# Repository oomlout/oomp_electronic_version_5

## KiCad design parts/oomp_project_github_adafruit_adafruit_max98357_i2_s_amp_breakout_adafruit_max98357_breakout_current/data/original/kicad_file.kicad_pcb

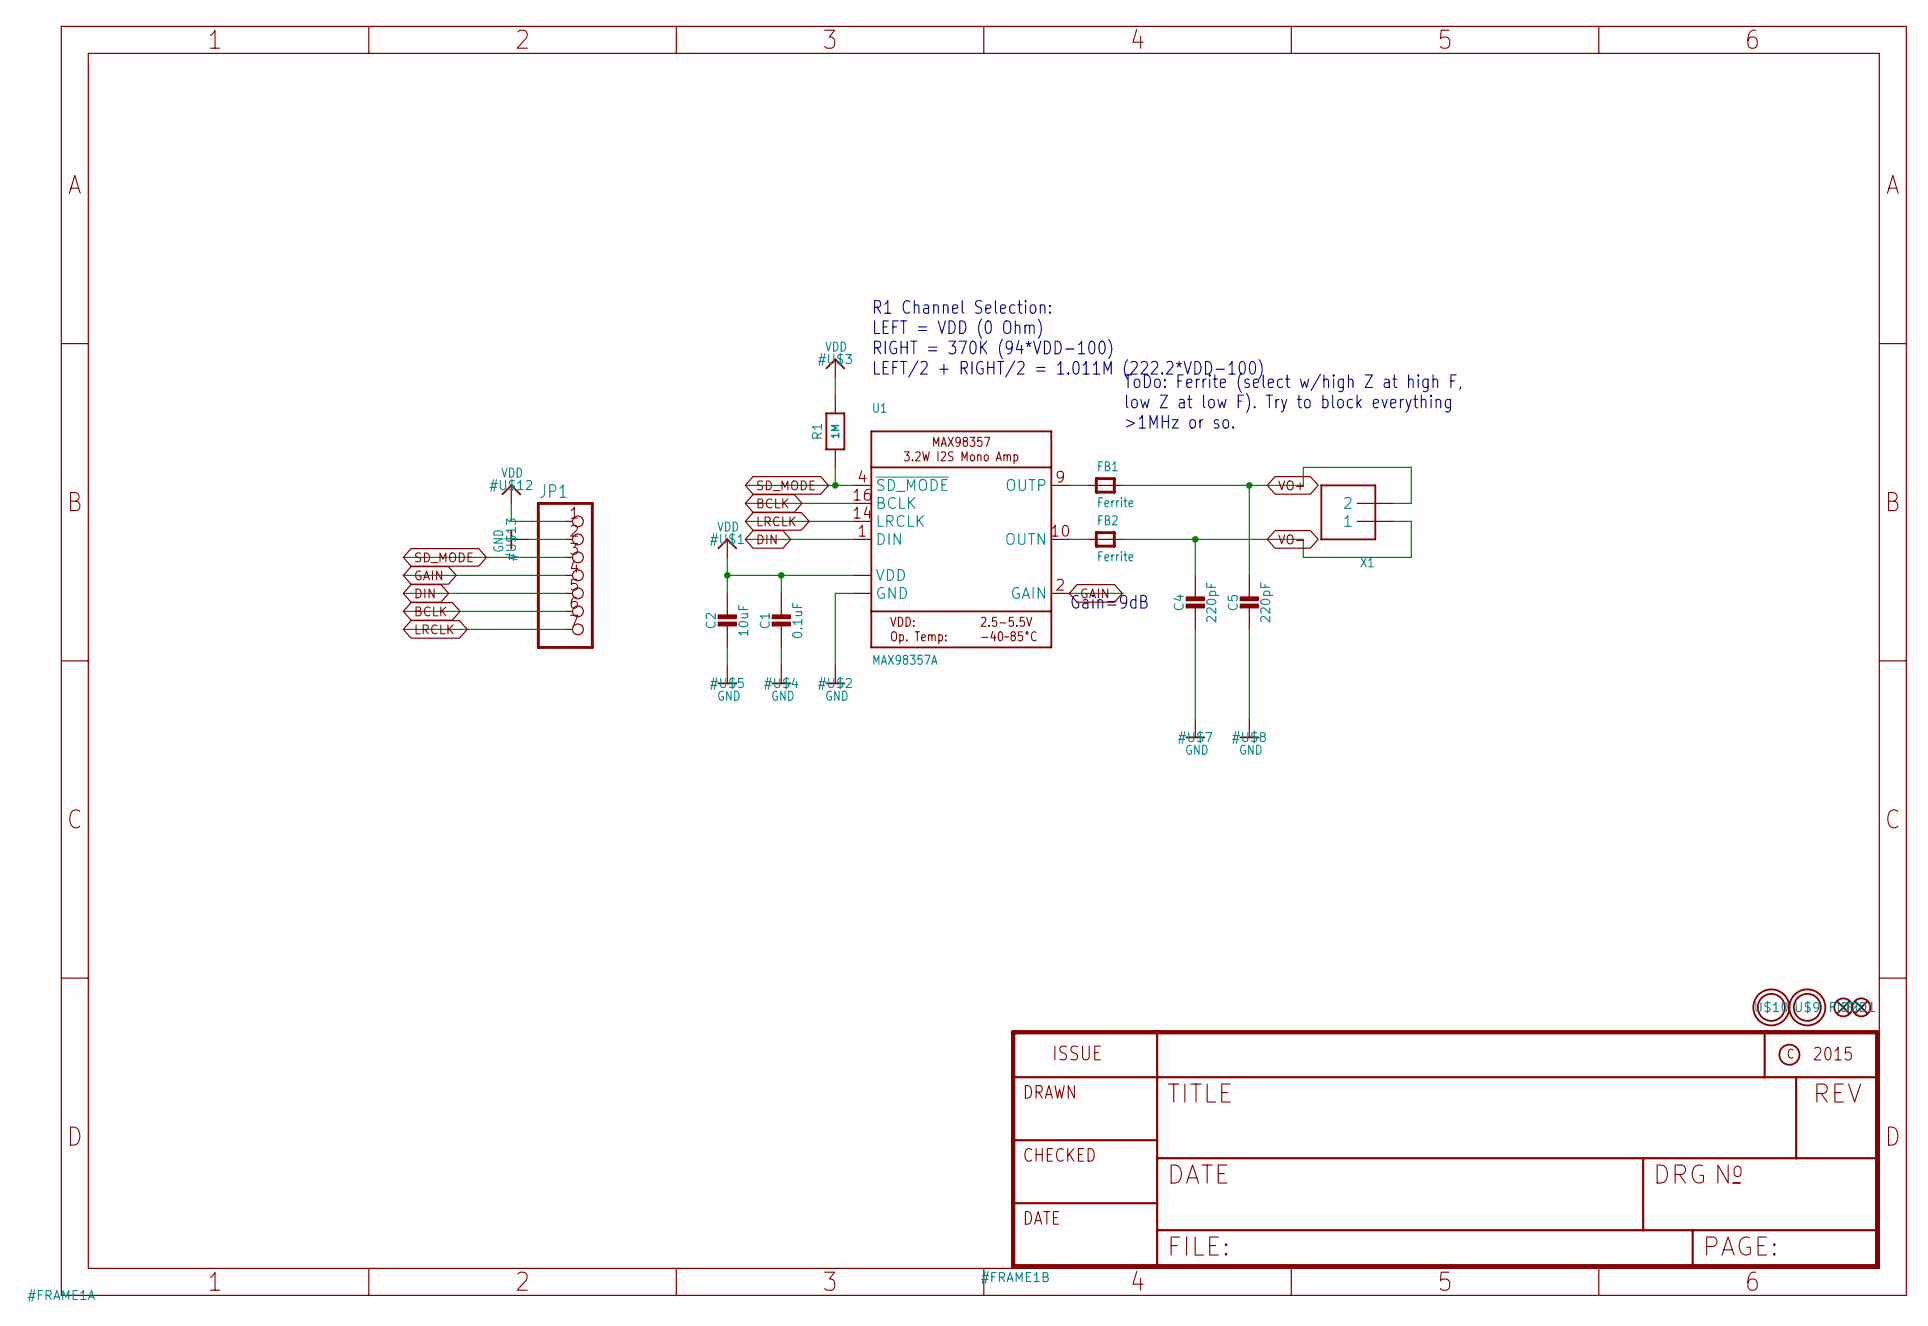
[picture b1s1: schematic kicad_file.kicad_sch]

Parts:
C1: 0.1uF; 0805-NO
C2: 10uF; 0805-NO
C4, C5: 220pF; 0805-NO
FB1, FB2: Ferrite; 0805-NO
FID1, FID2: FIDUCIAL""; FIDUCIAL_1MM
JP1: HEADER-1X7THICKER; 1X07_ROUND_76
R1: 1M; 0805-NO
U1: MAX98357A; QFN16_3MM
U$9, U$10: MOUNTINGHOLE2.5; MOUNTINGHOLE_2.5_PLATED
X1: TERMBLOCK_1X2; TERMBLOCK_1X2-3.5MM

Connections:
BCLK: JP1.6, U1.16 (BCLK)
DIN: JP1.5, U1.1 (DIN)
GAIN: JP1.4, U1.2 (GAIN)
GND: C1.2, C2.2, C4.2, C5.2, JP1.2, U1.3 (GND), U1.11 (GND), U1.15 (GND), U1.THERMAL (GND)
LRCLK: JP1.7, U1.14 (LRCLK)
unnamed: FB2.1, U1.10 (OUTN)
unnamed: FB1.1, U1.9 (OUTP)
SD_MODE: JP1.3, R1.1, U1.4 (~SD_MODE)
VDD: C1.1, C2.1, JP1.1, R1.2, U1.7 (VDD), U1.8 (VDD)
VO+: C5.1, FB1.2, X1.2
VO-: C4.1, FB2.2, X1.1

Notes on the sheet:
Gain=9dB
ToDo: Ferrite (select w/high Z at high F, low Z at low F). Try to block everything >1MHz or so.
R1 Channel Selection: LEFT = VDD (0 Ohm) RIGHT = 370K (94*VDD-100) LEFT/2 + RIGHT/2 = 1.011M (222.2*VDD-100)

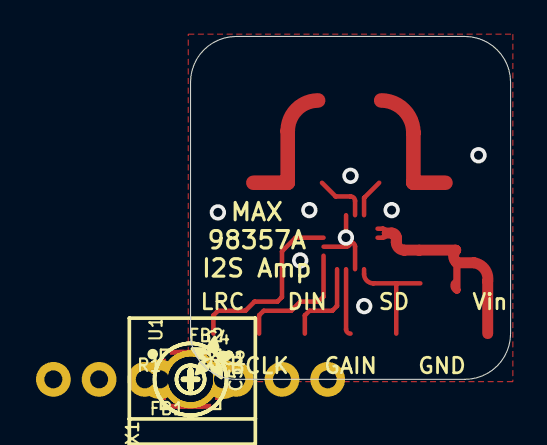
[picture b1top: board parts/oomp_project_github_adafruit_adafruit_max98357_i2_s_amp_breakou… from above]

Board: 2 copper layers, 17.8 x 19.1 mm, 18 parts (1 on the bottom side), 11 nets.

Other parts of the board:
U$6: SYMBOL_PLUS
U$11: SYMBOL_MINUS
U$14: ADAFRUIT_2.5MM
U$15: PCBFEAT-REV-040

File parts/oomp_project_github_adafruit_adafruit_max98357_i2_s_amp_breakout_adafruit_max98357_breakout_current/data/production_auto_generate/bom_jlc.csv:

Comment,Designator,Footprint,LCSC Part #
,JP1,Adafruit MAX98357 Breakout-import-fps:1X07_ROUND_76,C7501585
,U$14,Adafruit MAX98357 Breakout-import-fps:ADAFRUIT_2.5MM,
,U$15,Adafruit MAX98357 Breakout-import-fps:PCBFEAT-REV-040,
,U$11,Adafruit MAX98357 Breakout-import-fps:SYMBOL_MINUS,
,U$6,Adafruit MAX98357 Breakout-import-fps:SYMBOL_PLUS,
,X1,Adafruit MAX98357 Breakout-import-fps:TERMBLOCK_1X2-3.5MM,
0.1uF,C1,Adafruit MAX98357 Breakout-import-fps:0805-NO,
10uF,C2,Adafruit MAX98357 Breakout-import-fps:0805-NO,
1M,R1,Adafruit MAX98357 Breakout-import-fps:0805-NO,C2933280
220pF,"C4,C5",Adafruit MAX98357 Breakout-import-fps:0805-NO,
Ferrite,"FB1,FB2",Adafruit MAX98357 Breakout-import-fps:0805-NO,
MAX98357A,U1,Adafruit MAX98357 Breakout-import-fps:QFN16_3MM,

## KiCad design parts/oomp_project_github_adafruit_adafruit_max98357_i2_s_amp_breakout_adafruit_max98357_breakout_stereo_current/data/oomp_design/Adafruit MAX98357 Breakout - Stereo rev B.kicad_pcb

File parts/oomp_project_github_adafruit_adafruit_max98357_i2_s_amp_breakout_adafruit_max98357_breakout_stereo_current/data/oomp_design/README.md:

# OOMP KiCad design copy

Open `Adafruit MAX98357 Breakout - Stereo rev B.kicad_pro` (or the `.kicad_pcb` / `.kicad_sch`) in KiCad. Local OOMP libraries are under `libraries/`. Original inputs are preserved in [../original/](../original/).

Only verified unchanged installed KiCad defaults were renamed. Modified, custom, unmatched and unavailable items remain unchanged. Soldering variants are never swapped during conversion. Existing pad coordinates, nets and UUIDs are preserved.

See [conversion_report.yaml](conversion_report.yaml) for every conversion and skip. Copy this directory before editing; regeneration refuses to overwrite edited design files.

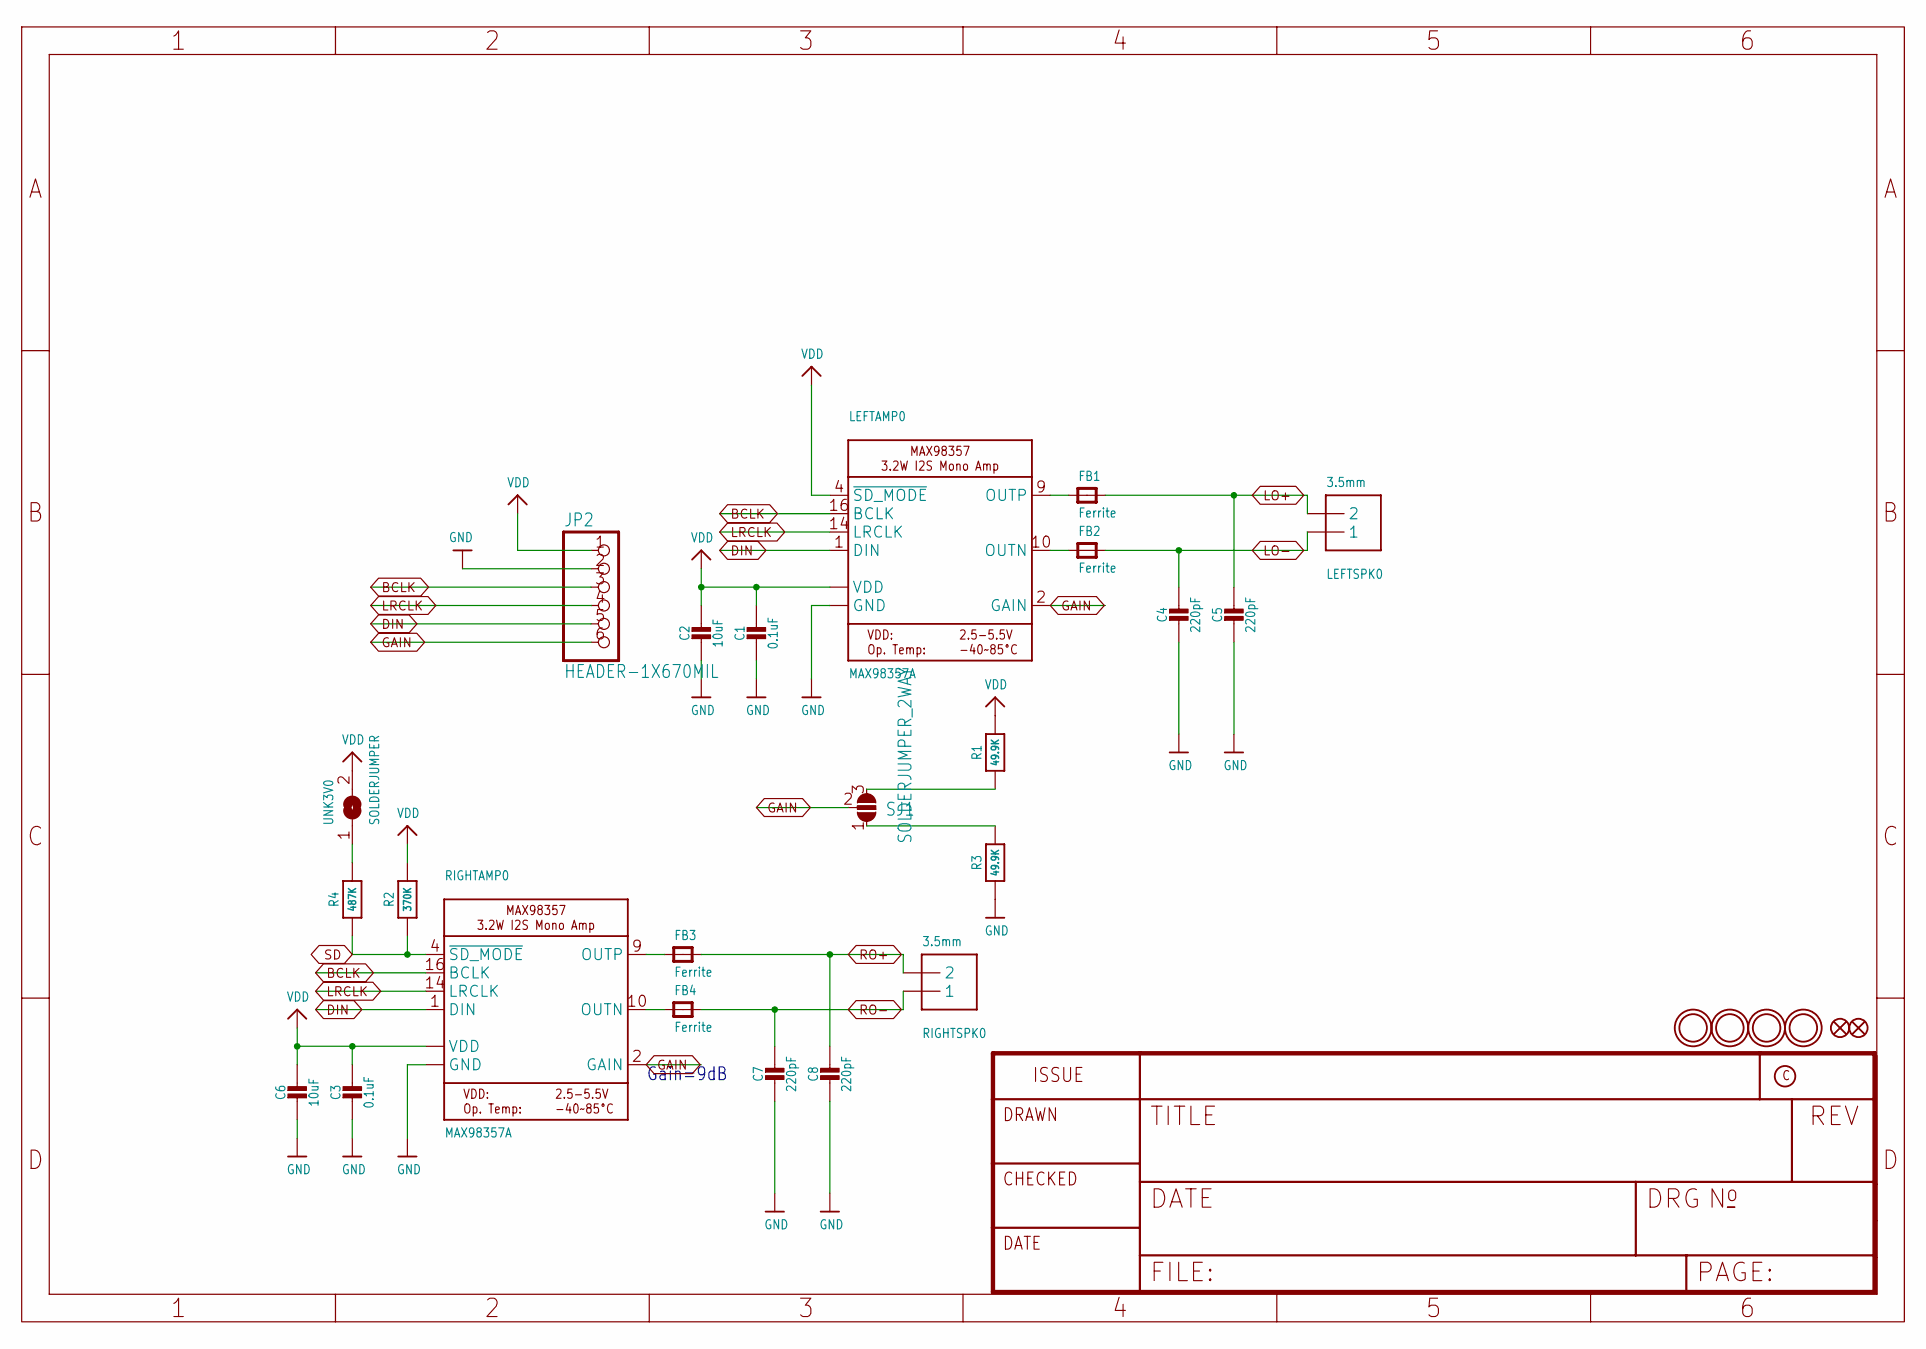
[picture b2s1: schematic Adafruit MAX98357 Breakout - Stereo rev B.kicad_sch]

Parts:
C1, C3: 0.1uF; 0603-NO
C2, C6: 10uF; 0805-NO
C4, C5, C7, C8: 220pF; 0603-NO
FB1, FB2, FB3, FB4: Ferrite; 0603-NO
FID1, FID2: FIDUCIAL_0.5MM
JP2: HEADER-1X670MIL; 1X06_ROUND_70
LEFTAMP0: MAX98357A; QFN16_3MM
LEFTSPK0: 3.5mm; TERMBLOCK_1X2-3.5MM
R1, R3: 49.9K; 0603-NO
R2: 370K; 0603-NO
R4: 487K; 0603-NO
RIGHTAMP0: MAX98357A; QFN16_3MM
RIGHTSPK0: 3.5mm; TERMBLOCK_1X2-3.5MM
SJ1: SOLDERJUMPER_2WAY; SOLDERJUMPER_2WAY_OPEN_NOPASTE
U$9, U$10, U$23, U$24: MOUNTINGHOLE2.5; MOUNTINGHOLE_2.5_PLATED
UNK3V0: SOLDERJUMPER; SOLDERJUMPER_ARROW_NOPASTE

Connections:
BCLK: JP2.3, LEFTAMP0.16 (BCLK), RIGHTAMP0.16 (BCLK)
DIN: JP2.5, LEFTAMP0.1 (DIN), RIGHTAMP0.1 (DIN)
GAIN: JP2.6, LEFTAMP0.2 (GAIN), RIGHTAMP0.2 (GAIN), SJ1.2
GND: C1.2, C2.2, C3.2, C4.2, C5.2, C6.2, C7.2, C8.2, JP2.2, LEFTAMP0.3 (GND), LEFTAMP0.11 (GND), LEFTAMP0.15 (GND), LEFTAMP0.THERMAL (GND), R3.1, RIGHTAMP0.3 (GND), RIGHTAMP0.11 (GND), RIGHTAMP0.15 (GND), RIGHTAMP0.THERMAL (GND)
LO+: C5.1, FB1.2, LEFTSPK0.2
LO-: C4.1, FB2.2, LEFTSPK0.1
LRCLK: JP2.4, LEFTAMP0.14 (LRCLK), RIGHTAMP0.14 (LRCLK)
unnamed: FB4.1, RIGHTAMP0.10 (OUTN)
unnamed: FB3.1, RIGHTAMP0.9 (OUTP)
unnamed: R3.2, SJ1.1
unnamed: R4.2, UNK3V0.1
unnamed: FB2.1, LEFTAMP0.10 (OUTN)
unnamed: FB1.1, LEFTAMP0.9 (OUTP)
unnamed: R1.1, SJ1.3
RO+: C8.1, FB3.2, RIGHTSPK0.2
RO-: C7.1, FB4.2, RIGHTSPK0.1
SD: R2.1, R4.1, RIGHTAMP0.4 (~SD_MODE)
VDD: C1.1, C2.1, C3.1, C6.1, JP2.1, LEFTAMP0.4 (~SD_MODE), LEFTAMP0.7 (VDD), LEFTAMP0.8 (VDD), R1.2, R2.2, RIGHTAMP0.7 (VDD), RIGHTAMP0.8 (VDD), UNK3V0.2

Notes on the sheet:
Gain=9dB

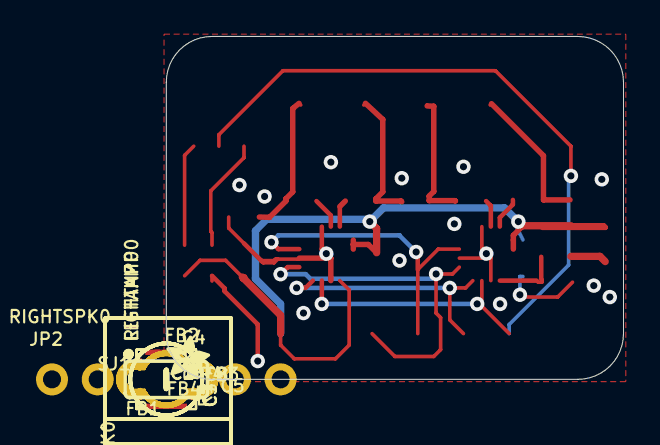
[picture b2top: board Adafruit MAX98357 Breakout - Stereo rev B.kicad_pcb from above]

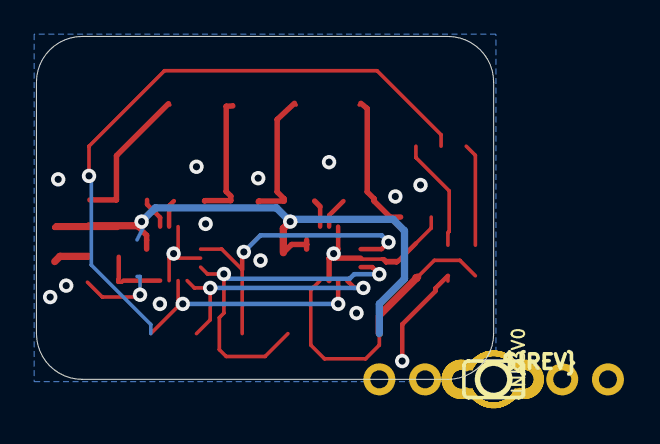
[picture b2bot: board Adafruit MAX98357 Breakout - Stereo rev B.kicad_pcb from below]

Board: 2 copper layers, 25.4 x 19.1 mm, 51 parts (6 on the bottom side), 18 nets.

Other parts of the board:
PLABEL0: PLABEL0
PLABEL1: PLABEL1
PLABEL2: PLABEL2
PLABEL3: PLABEL3
PLABEL4: PLABEL4
PLABEL5: PLABEL5
PLABEL6: PLABEL6
PLABEL7: PLABEL7
PLABEL8: PLABEL8
PLABEL9: PLABEL9
PLABEL10: PLABEL10
PLABEL11: PLABEL11
PLABEL12: PLABEL12
PLABEL13: PLABEL13
PLABEL14: PLABEL14
PLABEL15: PLABEL15
PLABEL16: PLABEL16
PLABEL17: PLABEL17
PLABEL18: PLABEL18
PLABEL19: PLABEL19
U$14: ADAFRUIT_2.5MM
U$15: PCBFEAT-REV-040

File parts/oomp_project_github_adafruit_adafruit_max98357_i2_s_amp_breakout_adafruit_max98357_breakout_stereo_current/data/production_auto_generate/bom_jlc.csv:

Comment,Designator,Footprint,LCSC Part #
,JP2,Adafruit MAX98357 Breakout - Stereo rev B-import-fps:1X06_ROUND_70,C37208
,U$14,Adafruit MAX98357 Breakout - Stereo rev B-import-fps:ADAFRUIT_2.5MM,
,U$15,Adafruit MAX98357 Breakout - Stereo rev B-import-fps:PCBFEAT-REV-040,
,PLABEL0,Adafruit MAX98357 Breakout - Stereo rev B-import-fps:PLABEL0,
,PLABEL1,Adafruit MAX98357 Breakout - Stereo rev B-import-fps:PLABEL1,
,PLABEL10,Adafruit MAX98357 Breakout - Stereo rev B-import-fps:PLABEL10,
,PLABEL11,Adafruit MAX98357 Breakout - Stereo rev B-import-fps:PLABEL11,
,PLABEL12,Adafruit MAX98357 Breakout - Stereo rev B-import-fps:PLABEL12,
,PLABEL13,Adafruit MAX98357 Breakout - Stereo rev B-import-fps:PLABEL13,
,PLABEL14,Adafruit MAX98357 Breakout - Stereo rev B-import-fps:PLABEL14,
,PLABEL15,Adafruit MAX98357 Breakout - Stereo rev B-import-fps:PLABEL15,
,PLABEL16,Adafruit MAX98357 Breakout - Stereo rev B-import-fps:PLABEL16,
,PLABEL17,Adafruit MAX98357 Breakout - Stereo rev B-import-fps:PLABEL17,
,PLABEL18,Adafruit MAX98357 Breakout - Stereo rev B-import-fps:PLABEL18,
,PLABEL19,Adafruit MAX98357 Breakout - Stereo rev B-import-fps:PLABEL19,
,PLABEL2,Adafruit MAX98357 Breakout - Stereo rev B-import-fps:PLABEL2,
,PLABEL3,Adafruit MAX98357 Breakout - Stereo rev B-import-fps:PLABEL3,
,PLABEL4,Adafruit MAX98357 Breakout - Stereo rev B-import-fps:PLABEL4,
,PLABEL5,Adafruit MAX98357 Breakout - Stereo rev B-import-fps:PLABEL5,
,PLABEL6,Adafruit MAX98357 Breakout - Stereo rev B-import-fps:PLABEL6,
,PLABEL7,Adafruit MAX98357 Breakout - Stereo rev B-import-fps:PLABEL7,
,PLABEL8,Adafruit MAX98357 Breakout - Stereo rev B-import-fps:PLABEL8,
,PLABEL9,Adafruit MAX98357 Breakout - Stereo rev B-import-fps:PLABEL9,
,UNK3V0,Adafruit MAX98357 Breakout - Stereo rev B-import-fps:SOLDERJUMPER_ARROW_NOPASTE,
0.1uF,"C1,C3",Adafruit MAX98357 Breakout - Stereo rev B-import-fps:0603-NO,C14663
10uF,"C2,C6",Adafruit MAX98357 Breakout - Stereo rev B-import-fps:0805-NO,
220pF,"C4,C5,C7,C8",Adafruit MAX98357 Breakout - Stereo rev B-import-fps:0603-NO,
3.5mm,"LEFTSPK0,RIGHTSPK0",Adafruit MAX98357 Breakout - Stereo rev B-import-fps:TERMBLOCK_1X2-3.5MM,
370K,R2,Adafruit MAX98357 Breakout - Stereo rev B-import-fps:0603-NO,
487K,R4,Adafruit MAX98357 Breakout - Stereo rev B-import-fps:0603-NO,
49.9K,"R1,R3",Adafruit MAX98357 Breakout - Stereo rev B-import-fps:0603-NO,
Ferrite,"FB1,FB2,FB3,FB4",Adafruit MAX98357 Breakout - Stereo rev B-import-fps:0603-NO,
MAX98357A,"LEFTAMP0,RIGHTAMP0",Adafruit MAX98357 Breakout - Stereo rev B-import-fps:QFN16_3MM,

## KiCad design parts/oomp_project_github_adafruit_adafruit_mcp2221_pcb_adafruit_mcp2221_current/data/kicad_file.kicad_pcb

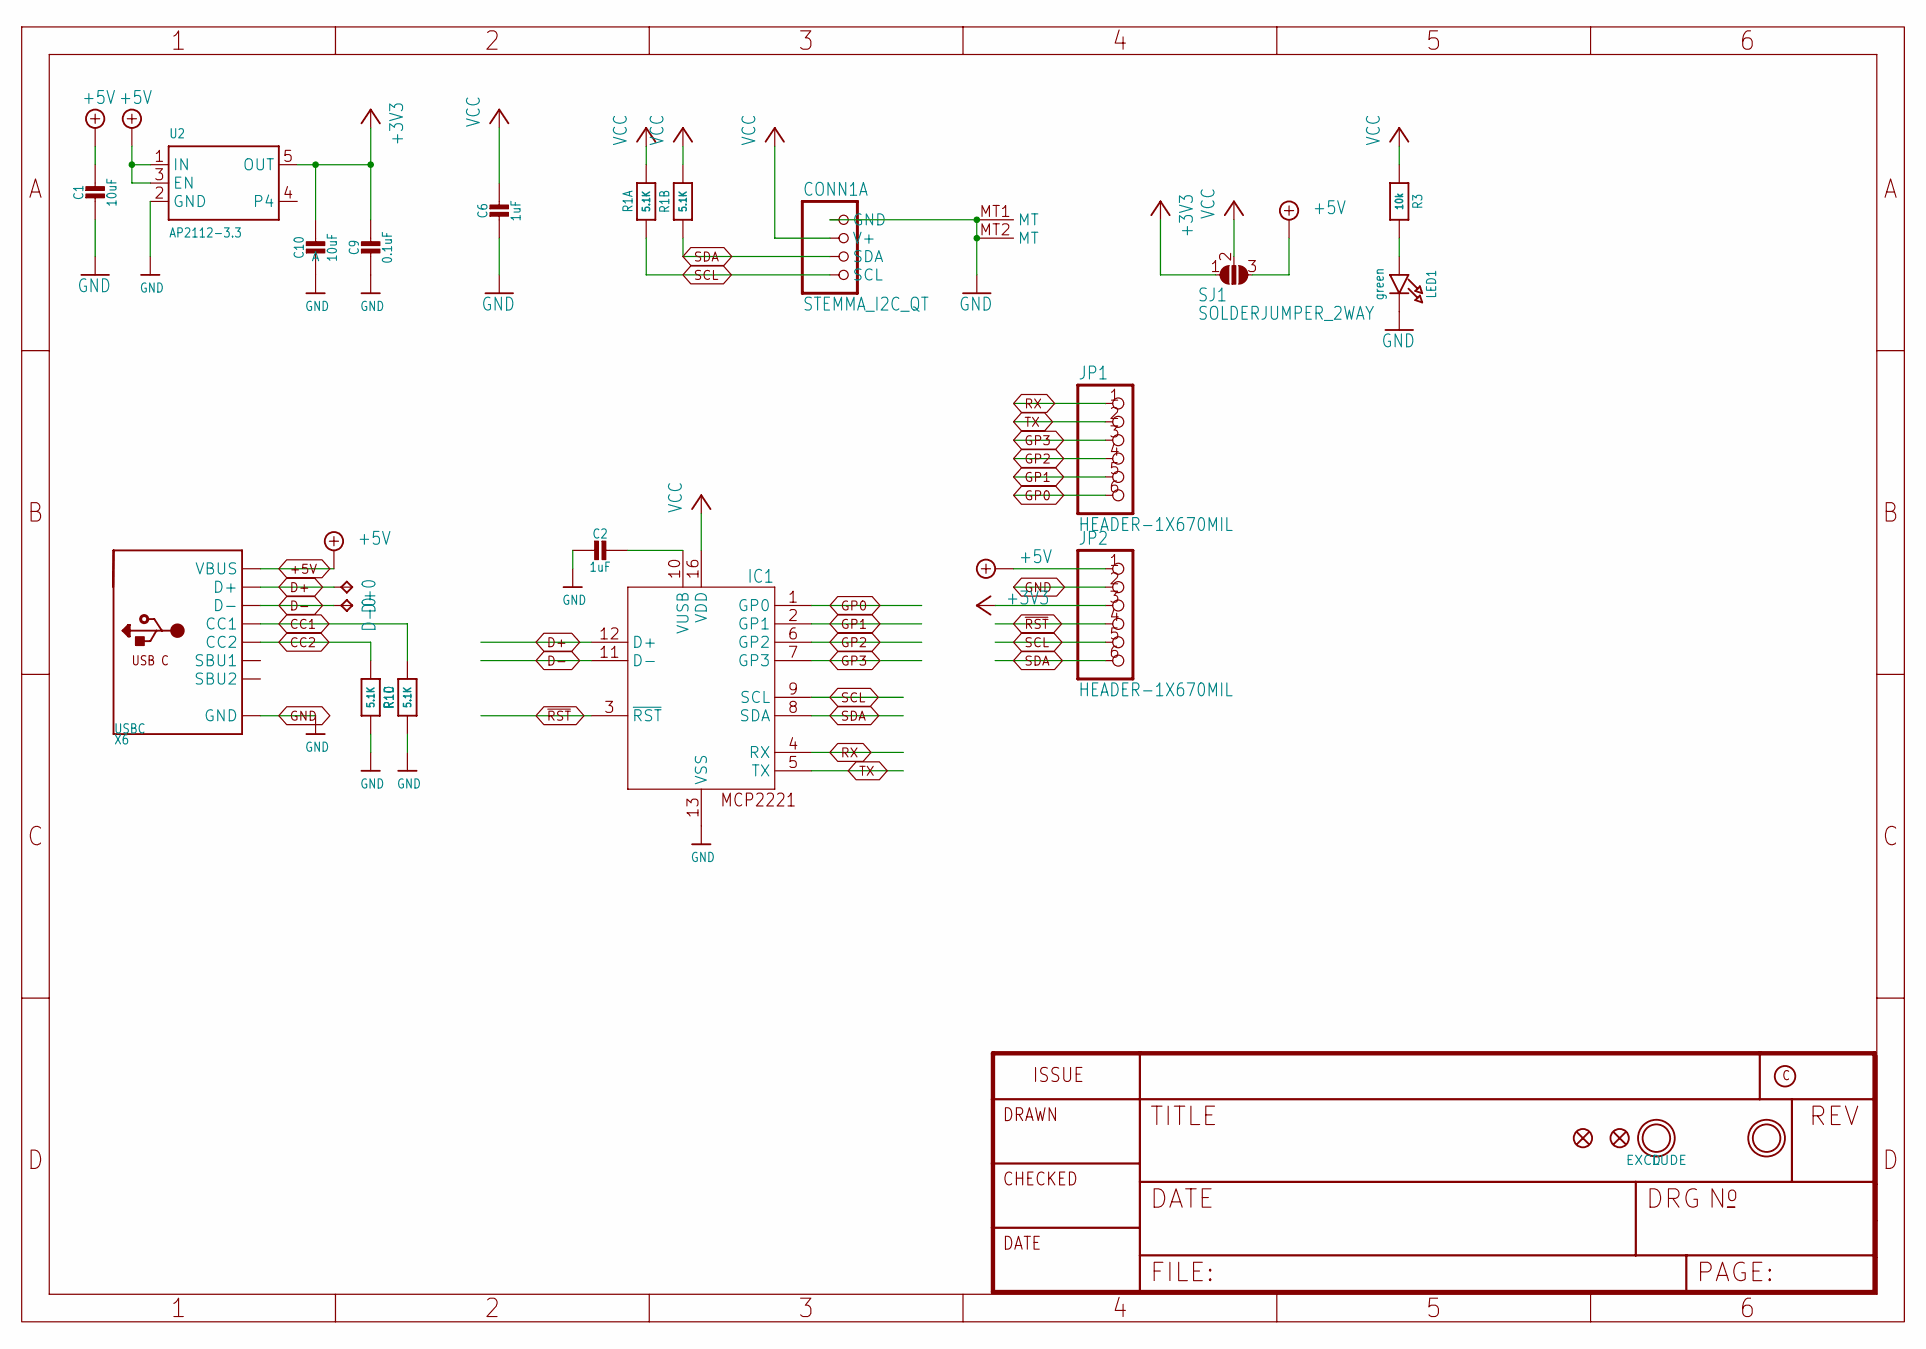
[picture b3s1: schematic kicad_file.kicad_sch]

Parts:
C1, C10: 10uF; 0805-NO
C2, C6: 1uF; 0603-NO
C9: 0.1uF; 0603-NO
CONN1: STEMMA_I2C_QT; JST_SH4
D+0: TPTP17R; TP17R
D-0: TPTP17R; TP17R
FID1, FID2: FIDUCIAL_1MM
IC1: MCP2221_ML; QFN16_4MM
JP1, JP2: HEADER-1X670MIL; 1X06_ROUND_70
LED1: green; CHIPLED_0603_NOOUTLINE
R1: 5.1K; RESPACK_4X0603
R3: 10k; 0603-NO
SJ1: SOLDERJUMPER_2WAY; SOLDERJUMPER_2WAY_OPEN_NOPASTE
U2: AP2112-3.3; SOT23-5
U$6, U$7: MOUNTINGHOLE2.5; MOUNTINGHOLE_2.5_PLATED
X6: USBC; USB_C_CUSB31-CFM2AX-01-X

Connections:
+3V3: C9.1, C10.1, JP2.3, SJ1.1, U2.5 (OUT)
+5V: C1.1, JP2.1, SJ1.3, U2.1 (IN), U2.3 (EN), X6.A4B9 (VBUS), X6.B4A9 (VBUS)
CC1: R1.6 (2), X6.A5 (CC1)
CC2: R1.4 (1), X6.B5 (CC2)
D+: D+0.TP, IC1.12 (D+), X6.A6 (D+), X6.B6 (D+)
D-: D-0.TP, IC1.11 (D-), X6.A7 (D-), X6.B7 (D-)
GND: C1.2, C2.2, C6.2, C9.2, C10.2, CONN1.1 (GND), CONN1.MT1 (MT), CONN1.MT2 (MT), IC1.13 (VSS), JP2.2, LED1.C, R1.3 (1), R1.5 (2), U2.2 (GND), X6.A1B12 (GND), X6.B1A12 (GND)
GP0: IC1.1 (GP0), JP1.6
GP1: IC1.2 (GP1), JP1.5
GP2: IC1.6 (GP2), JP1.4
GP3: IC1.7 (GP3), JP1.3
unnamed: C2.1, IC1.10 (VUSB)
unnamed: LED1.A, R3.2
RX: IC1.4 (RX), JP1.1
SCL: CONN1.4 (SCL), IC1.9 (SCL), JP2.5, R1.1
SDA: CONN1.3 (SDA), IC1.8 (SDA), JP2.6, R1.2 (1)
TX: IC1.5 (TX), JP1.2
VCC: C6.1, CONN1.2 (V+), IC1.16 (VDD), R1.7 (2), R1.8 (2), R3.1, SJ1.2
~RST: IC1.3 (~RST), JP2.4

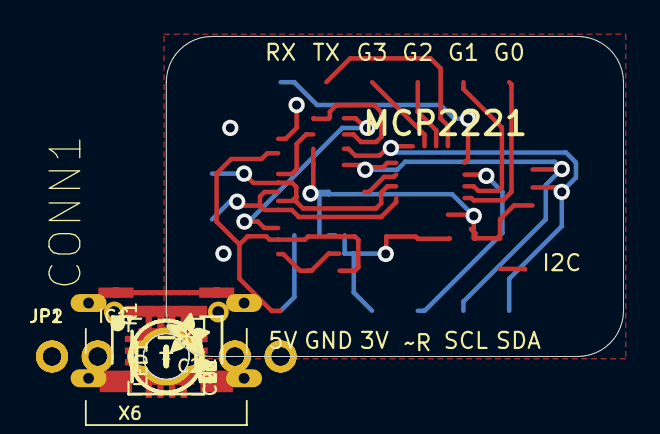
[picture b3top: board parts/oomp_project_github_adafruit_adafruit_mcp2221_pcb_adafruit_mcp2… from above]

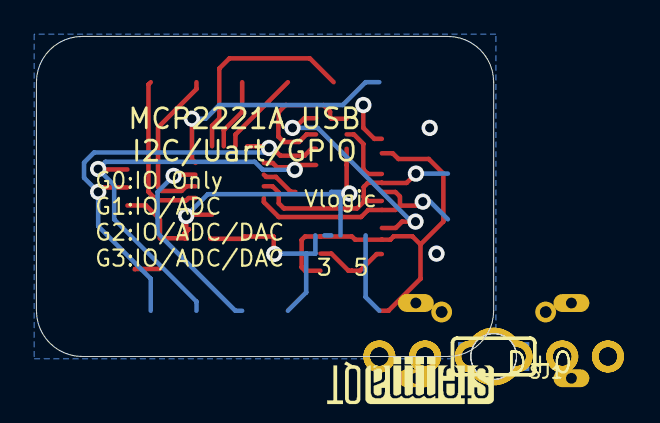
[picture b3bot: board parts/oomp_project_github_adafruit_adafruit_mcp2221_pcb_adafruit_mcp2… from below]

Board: 2 copper layers, 25.4 x 17.8 mm, 25 parts (4 on the bottom side), 19 nets.

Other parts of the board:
U$2: ADAFRUIT_2.5MM
U$3: STEMMAQT
UNK_HOLE_0: dummyfp0
UNK_HOLE_1: dummyfp1

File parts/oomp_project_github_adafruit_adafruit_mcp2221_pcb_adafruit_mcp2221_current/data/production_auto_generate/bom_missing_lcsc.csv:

Designator,Comment,Footprint,OOMP ID,Reason
C1,10uF,Adafruit MCP2221-import-fps:0805-NO,electronic_capacitor_0805_10_micro_farad,No verified LCSC part number
C10,10uF,Adafruit MCP2221-import-fps:0805-NO,electronic_capacitor_0805_10_micro_farad,No verified LCSC part number
D+0,TPTP17R,Adafruit MCP2221-import-fps:TP17R,,No verified LCSC part number
D-0,TPTP17R,Adafruit MCP2221-import-fps:TP17R,,No verified LCSC part number
IC1,MCP2221_ML,Adafruit MCP2221-import-fps:QFN16_4MM,,No verified LCSC part number
LED1,green,Adafruit MCP2221-import-fps:CHIPLED_0603_NOOUTLINE,electronic_led_0603_green,No verified LCSC part number
U2,AP2112-3.3,Adafruit MCP2221-import-fps:SOT23-5,,No verified LCSC part number
U$2,,Adafruit MCP2221-import-fps:ADAFRUIT_2.5MM,,No verified LCSC part number
U$3,,Adafruit MCP2221-import-fps:STEMMAQT,,No verified LCSC part number
X6,USBC,Adafruit MCP2221-import-fps:USB_C_CUSB31-CFM2AX-01-X,,No verified LCSC part number

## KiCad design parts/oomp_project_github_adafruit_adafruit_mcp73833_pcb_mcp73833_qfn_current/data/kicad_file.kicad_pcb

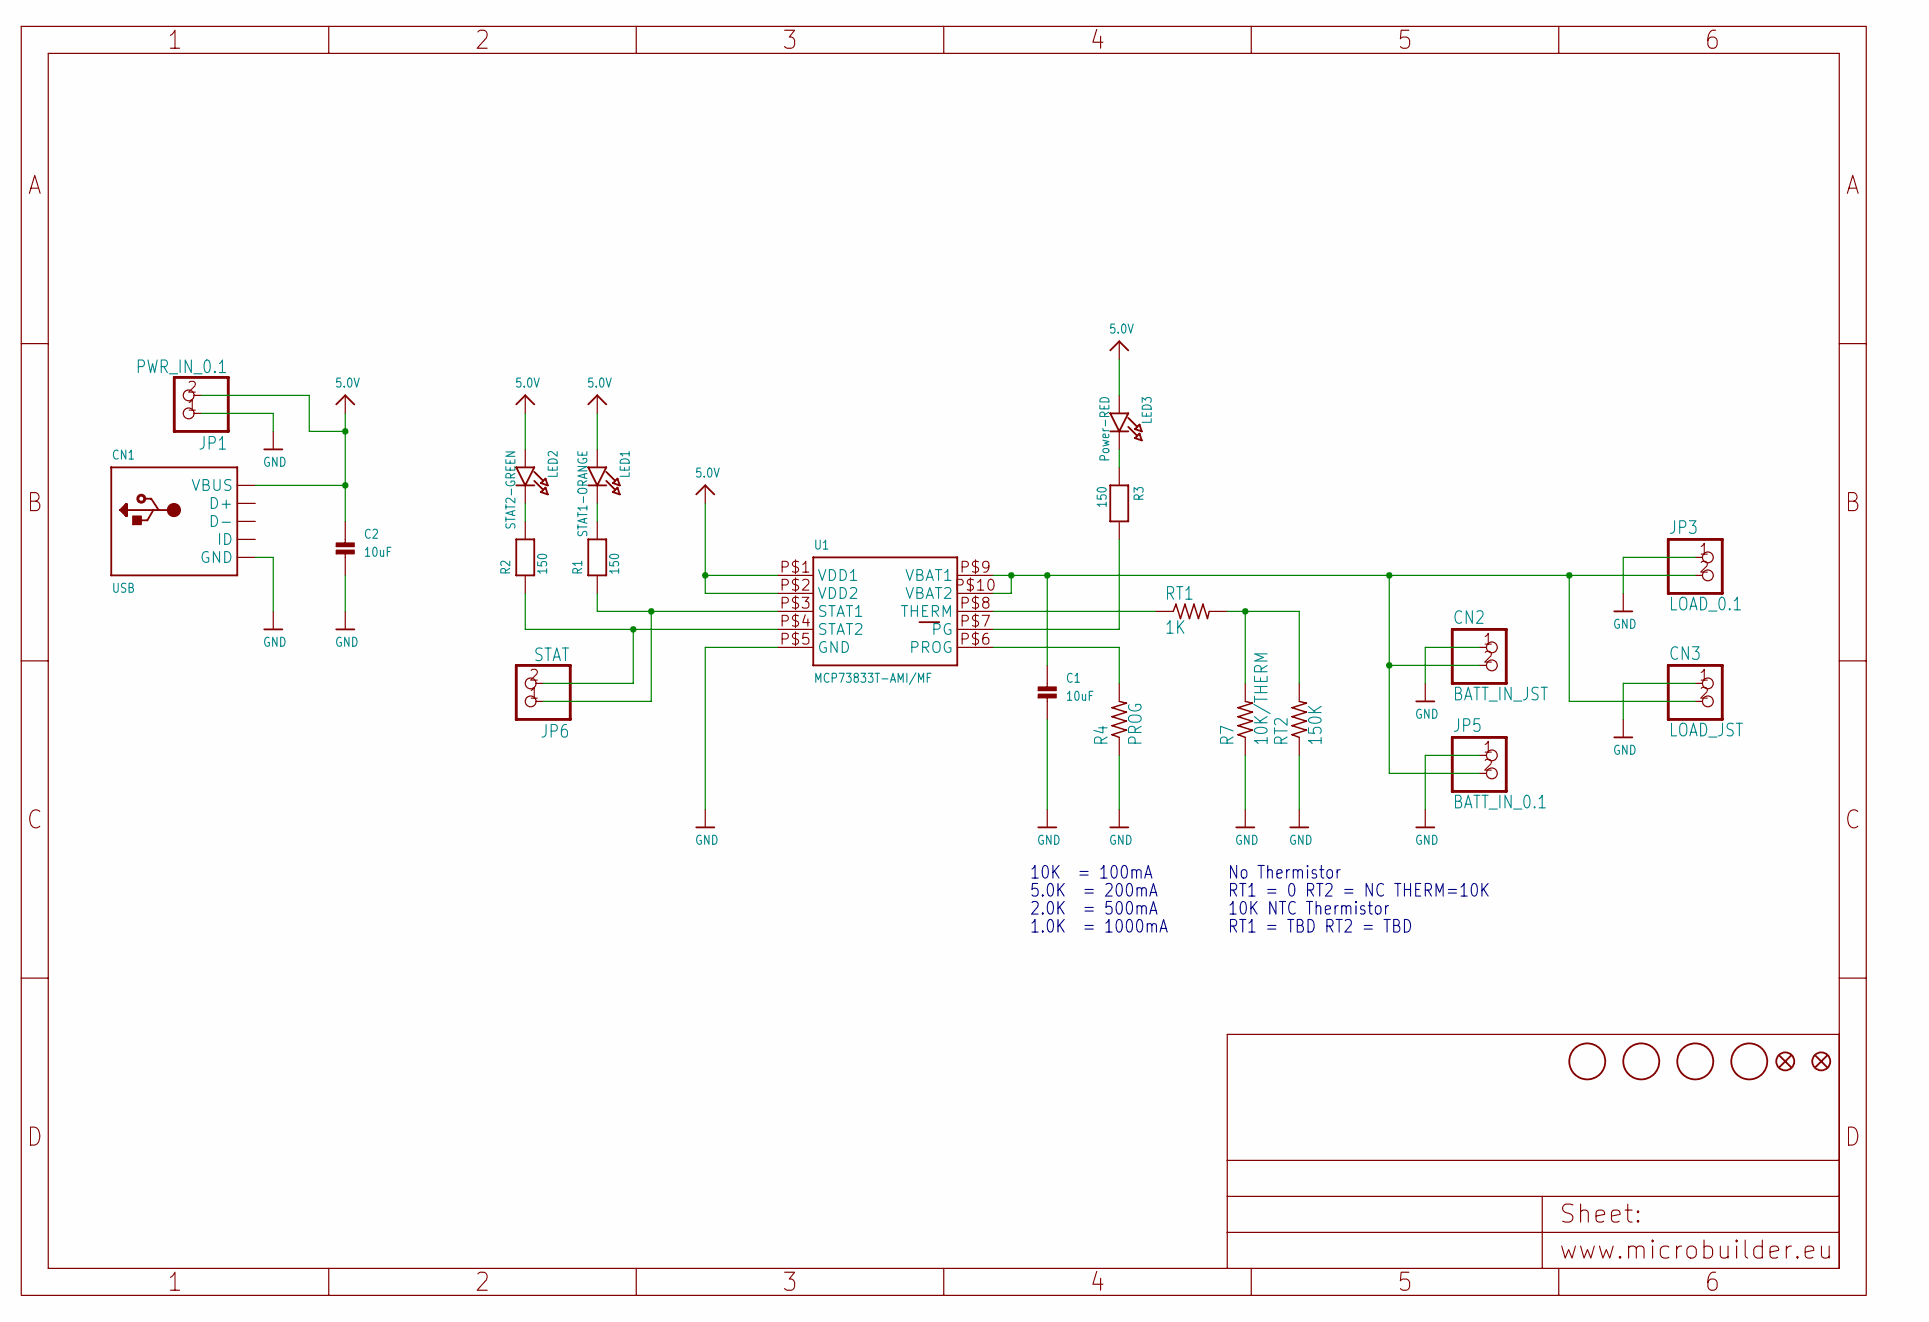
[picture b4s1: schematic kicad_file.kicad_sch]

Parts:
C1, C2: 10uF; 0805
CN1: USB; USB-MINIB_LARGER
CN2: BATT_IN_JST; JSTPH2
CN3: LOAD_JST; JSTPH2
JP1: PWR_IN_0.1; 1X02_OVAL
JP2, JP4: FIDUCIAL1.5X3; FIDUCIAL-1X2.5
JP3: LOAD_0.1; 1X02_OVAL
JP5: BATT_IN_0.1; 1X02_OVAL
JP6: STAT; 1X02_OVAL
LED1: STAT1-ORANGE; CHIPLED_0805
LED2: STAT2-GREEN; CHIPLED_0805
LED3: Power-RED; CHIPLED_0805
R1, R2, R3: 150; 0805
R4: PROG; 0805-THM
R7: 10K/THERM; 0805-THM
RT1: 1K; R0805
RT2: 150K; R0805
U1: MCP73833T-AMI/MF; DFN10_3X3MM
U$11, U$16, U$18, U$19: MOUNTINGHOLE2.0; MOUNTINGHOLE_2.0_PLATED

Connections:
5.0V: C2.1, CN1.VBUS, JP1.2, LED1.A, LED2.A, LED3.A, U1.P$1 (VDD1), U1.P$2 (VDD2)
BATT: C1.1, CN2.2, CN3.2, JP3.2, JP5.2, U1.P$9 (VBAT1), U1.P$10 (VBAT2)
GND: C1.2, C2.2, CN1.GND, CN2.1, CN3.1, JP1.1, JP3.1, JP5.1, R4.1, R7.1, RT2.1, U1.P$5 (GND)
unnamed: LED1.C, R1.2
unnamed: LED2.C, R2.2
unnamed: JP6.1, R1.1, U1.P$3 (STAT1)
unnamed: JP6.2, R2.1, U1.P$4 (STAT2)
unnamed: RT1.1, U1.P$8 (THERM)
unnamed: R3.2, U1.P$7 (PG)
unnamed: R7.2, RT1.2, RT2.2
unnamed: LED3.C, R3.1
unnamed: R4.2, U1.P$6 (PROG)

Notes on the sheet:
No Thermistor
10K = 100mA
10K NTC Thermistor
2.0K = 500mA
5.0K = 200mA
1.0K = 1000mA
RT1 = 0 RT2 = NC THERM=10K
RT1 = TBD RT2 = TBD

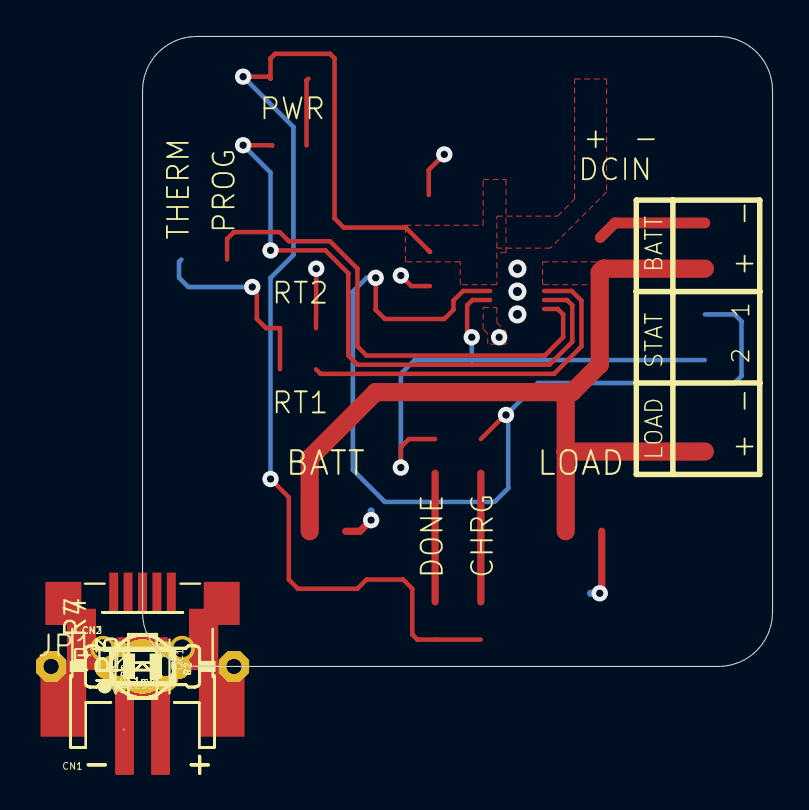
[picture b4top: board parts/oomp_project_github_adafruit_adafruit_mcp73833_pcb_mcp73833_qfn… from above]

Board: 2 copper layers, 35.0 x 35.0 mm, 27 parts (1 on the bottom side), 12 nets.

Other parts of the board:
U$14: ADAFRUIT200MIL

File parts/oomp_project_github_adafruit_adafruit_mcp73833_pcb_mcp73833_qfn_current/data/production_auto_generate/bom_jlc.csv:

Comment,Designator,Footprint,LCSC Part #
,U$14,MCP73833_QFN_v1.0-import-fps:ADAFRUIT200MIL,
10K/THERM,R7,MCP73833_QFN_v1.0-import-fps:0805-THM,C17414
10uF,"C1,C2",MCP73833_QFN_v1.0-import-fps:0805,
150,"R1,R2,R3",MCP73833_QFN_v1.0-import-fps:0805,C2907300
150K,RT2,MCP73833_QFN_v1.0-import-fps:R0805,C2907228
1K,RT1,MCP73833_QFN_v1.0-import-fps:R0805,C17513
BATT_IN_0.1,JP5,MCP73833_QFN_v1.0-import-fps:1X02_OVAL,C492401
BATT_IN_JST,CN2,MCP73833_QFN_v1.0-import-fps:JSTPH2,
FIDUCIAL1.5X3,"JP2,JP4",MCP73833_QFN_v1.0-import-fps:FIDUCIAL-1X2.5,
LOAD_0.1,JP3,MCP73833_QFN_v1.0-import-fps:1X02_OVAL,C492401
LOAD_JST,CN3,MCP73833_QFN_v1.0-import-fps:JSTPH2,
MCP73833T-AMI/MF,U1,MCP73833_QFN_v1.0-import-fps:DFN10_3X3MM,
Power-RED,LED3,MCP73833_QFN_v1.0-import-fps:CHIPLED_0805,
PROG,R4,MCP73833_QFN_v1.0-import-fps:0805-THM,
PWR_IN_0.1,JP1,MCP73833_QFN_v1.0-import-fps:1X02_OVAL,C492401
STAT,JP6,MCP73833_QFN_v1.0-import-fps:1X02_OVAL,C492401
STAT1-ORANGE,LED1,MCP73833_QFN_v1.0-import-fps:CHIPLED_0805,
STAT2-GREEN,LED2,MCP73833_QFN_v1.0-import-fps:CHIPLED_0805,
USB,CN1,MCP73833_QFN_v1.0-import-fps:USB-MINIB_LARGER,
